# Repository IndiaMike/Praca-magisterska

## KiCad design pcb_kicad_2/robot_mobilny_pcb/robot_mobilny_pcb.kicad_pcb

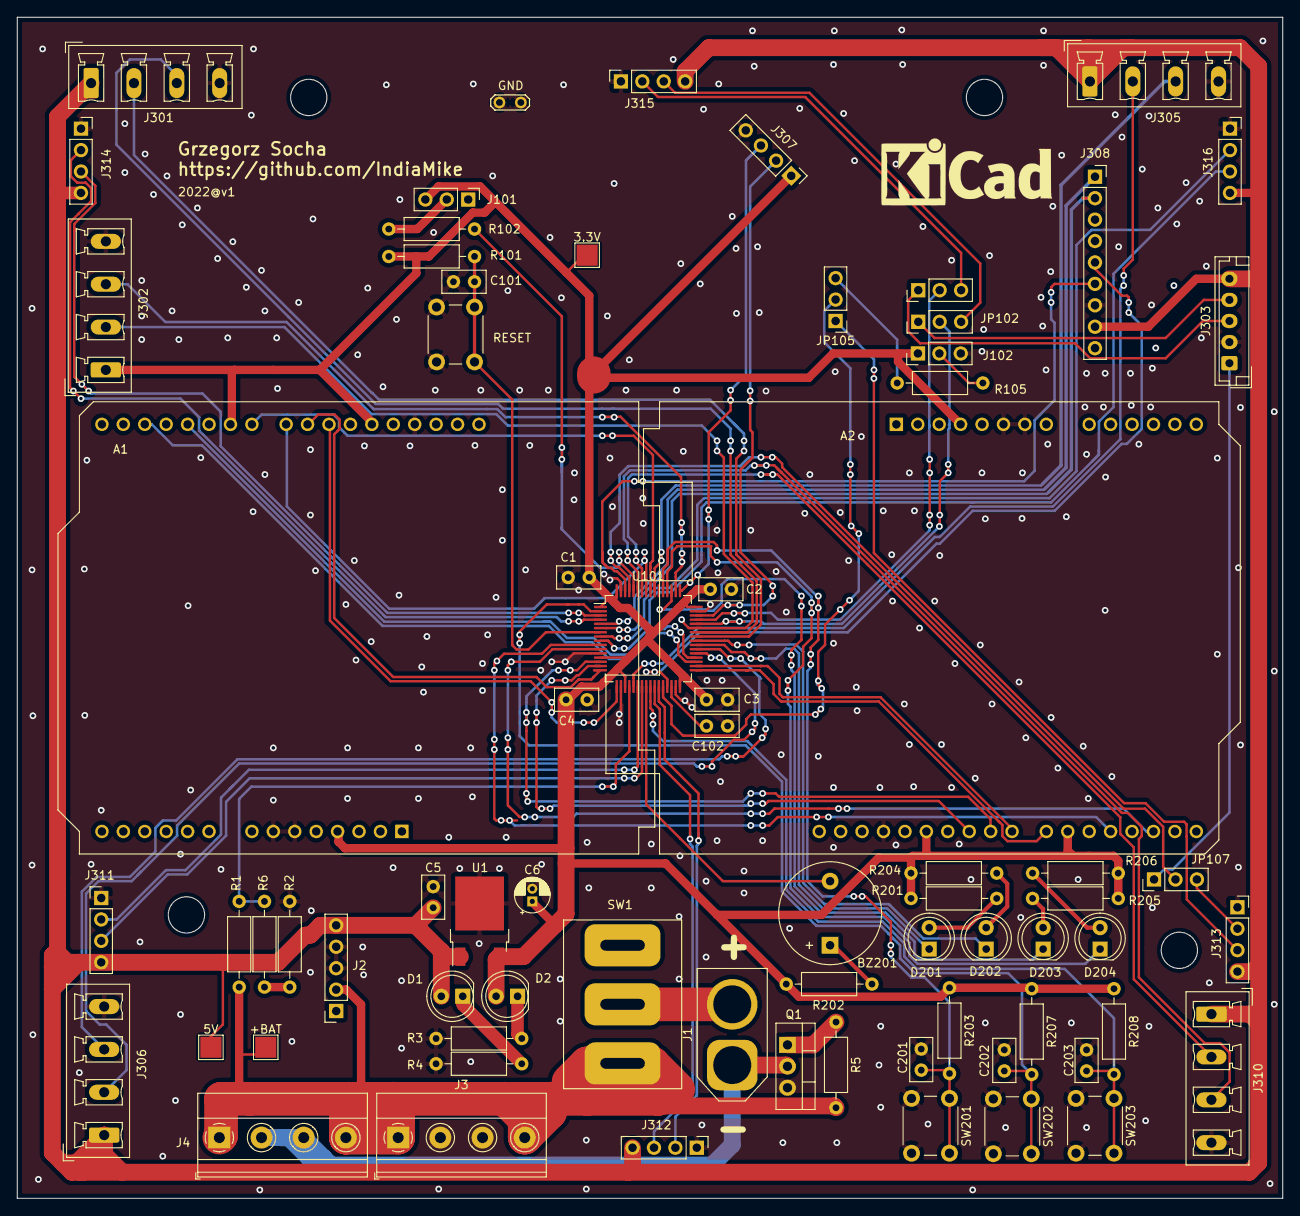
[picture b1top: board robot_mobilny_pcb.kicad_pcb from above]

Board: 2 copper layers, 150.0 x 140.0 mm, 73 parts (0 on the bottom side), 77 nets.

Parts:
3.3V, 5V: T; TestPoint_Pad_2.5x2.5mm
+BAT: T; TestPoint_Pad_2.5x2.5mm
A1, A2: Arduino_UNO_R3
BZ201: Buzzer; Buzzer_12x9.5RM7.6
C1, C2, C3, C4, C5, C101, C201, C202, C203: 100nF; C_Disc_D5.0mm_W2.5mm_P2.50mm
C6: 2,2uF; CP_Radial_D4.0mm_P1.50mm
C102: 4.7uF; C_Disc_D5.0mm_W2.5mm_P2.50mm
D1: RED; LED_D5.0mm
D2: RED2; LED_D5.0mm
D201, D202, D203: LED_G; LED_D5.0mm
D204: LED_Y; LED_D5.0mm
GND: TestPoint_2Pads_Pitch2.54mm_Drill0.8mm
J1: Power 14.8V; AMASS_XT60-M_1x02_P7.20mm_Vertical
J2: STEP_DOWN_D24V50F5; PinSocket_1x05_P2.54mm_Vertical
J3: Motor Driver Power; TerminalBlock_Phoenix_MKDS-1,5-4_1x04_P5.00mm_Horizontal
J4: Motor Driver Power_not_reverse; TerminalBlock_Phoenix_MKDS-1,5-4_1x04_P5.00mm_Horizontal
J101: BOOT0; PinHeader_1x03_P2.54mm_Vertical
J102: BOOT1; PinHeader_1x03_P2.54mm_Vertical
J301: ENCODER_MOT_1; PhoenixContact_MCV_1,5_4-G-5.08_1x04_P5.08mm_Vertical
J302: UART_WIFI; PhoenixContact_MCV_1,5_4-G-5.08_1x04_P5.08mm_Vertical
J303: LIDAR XH2.54-5P; JST_EH_B5B-EH-A_1x05_P2.50mm_Vertical
J305: ENCODER_MOT_2; PhoenixContact_MCV_1,5_4-G-5.08_1x04_P5.08mm_Vertical
J306: ENCODER_MOT_3; PhoenixContact_MCV_1,5_4-G-5.08_1x04_P5.08mm_Vertical
J307: SWD; PinHeader_1x04_P2.54mm_Vertical
J308: LSM303D_acc+mag; PinSocket_1x09_P2.54mm_Vertical
J310: ENCODER_MOT_4; PhoenixContact_MCV_1,5_4-G-5.08_1x04_P5.08mm_Vertical
J311, J312: Conn_01x04_Female; PinHeader_1x04_P2.54mm_Vertical
J313, J314, J315, J316: Conn_01x04_Female; PinSocket_1x04_P2.54mm_Vertical
JP102, JP105, JP107: Jumper_3_Bridged12; PinHeader_1x03_P2.54mm_Vertical
JP104: Zwora; PinHeader_1x03_P2.54mm_Vertical
Q1: IRF540N; TO-220-3_Vertical
R1: 100k; R_Axial_DIN0207_L6.3mm_D2.5mm_P10.16mm_Horizontal
R2, R6, R101, R102, R105: 10k; R_Axial_DIN0207_L6.3mm_D2.5mm_P10.16mm_Horizontal
R3, R4: 470; R_Axial_DIN0207_L6.3mm_D2.5mm_P10.16mm_Horizontal
R5: 47k; R_Axial_DIN0207_L6.3mm_D2.5mm_P10.16mm_Horizontal
R201, R202, R204, R205, R206: 330; R_Axial_DIN0207_L6.3mm_D2.5mm_P10.16mm_Horizontal
R203, R207, R208: 4k7; R_Axial_DIN0207_L6.3mm_D2.5mm_P10.16mm_Horizontal
RESET: RESET; SW_PUSH_6mm_H9.5mm
SW1: SWITCH; Button_MRS-101
SW201: Button_1; SW_PUSH_6mm_H9.5mm
SW202: Button_2; SW_PUSH_6mm_H9.5mm
SW203: Button_3; SW_PUSH_6mm_H9.5mm
U1: LF33_TO252; TO-252-2
U101: STM32F411RETx; LQFP-64_10x10mm_P0.5mm

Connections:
+3V3: 3.3V.1, A1.4, A1.21, A1.27, A2.4, A2.21, A2.27, C1.1, C2.1, C3.1, C4.1, C6.1, D2.2, J101.3, J102.1, J302.1, J307.1, R101.2, R201.2, R202.1, R203.1, R204.2, R205.2, R206.2, R207.1, R208.1, U1.3, U101.1, U101.13, U101.19, U101.32, U101.48, U101.64
+5V: 5V.1, C5.1, D1.2, J2.5, J301.1, J303.5, J305.1, J306.1, J308.8, J310.1, J311.4, J312.4, J313.4, J314.4, J315.4, J316.4, U1.1
+BATT: +BAT.1, J2.2, J3.1, J3.4, J4.1, J4.4, R1.1, R5.2, SW1.3
ADC_BAT: R1.2, R2.1, U101.20
BOOT0: R102.1, U101.60
BUTTON_1: C201.2, R203.2, SW201.1, U101.53
BUTTON_2: C202.2, R207.2, SW202.1, U101.2
BUTTON_3: C203.2, R208.2, SW203.1, U101.25
BUZZER: BZ201.2, U101.24
Dist_Sens_01_Echo: J311.2, U101.22
Dist_Sens_01_Trig: J311.3, U101.23
Dist_Sens_02_Echo: J312.2, U101.27
Dist_Sens_02_Trig: J312.3, U101.26
Dist_Sens_03_Echo: J313.2, JP107.3
Dist_Sens_03_Trig: J313.3, JP105.1
Dist_Sens_04_Echo: J314.2, U101.4
Dist_Sens_04_Trig: J314.3, U101.3
Dist_Sens_05_Echo: J316.2, U101.8
Dist_Sens_05_Trig: J316.3, U101.9
Dist_Sens_06_Echo: J315.2, JP104.3
Dist_Sens_06_Trig: J315.3, JP102.3
ENCODER_1_A: J301.2, U101.41
ENCODER_1_B: J301.3, U101.42
ENCODER_2_A: J305.2, U101.21
ENCODER_2_B: J305.3, U101.55
ENCODER_3_A: J306.2, U101.37
ENCODER_3_B: J306.3, U101.38
ENCODER_4_A: J310.2, U101.58
ENCODER_4_B: J310.3, U101.59
GND: A1.6, A1.7, A1.29, A2.6, A2.7, A2.29, C1.2, C2.2, C3.2, C4.2, C5.2, C6.2, C101.2, C102.2, C201.1, C202.1, C203.1, GND.1, GND.2, J2.3, J2.4, J3.2, J3.3, J101.1, J102.3, J301.4, J302.4, J303.2, J305.4, J306.4, J307.4, J308.7, J310.4, J311.1, J312.1, J313.1, J314.1, J315.1, J316.1, Q1.3, R3.2, R4.2, R6.2, RESET.2, SW201.2, SW202.2, SW203.2, U1.2, U101.12, U101.18, U101.31, U101.47, U101.63
I2C2_SCL_mag+acc: J308.5, U101.29
I2C2_SDA_mag+acc: J308.6, U101.62
INT1_mag+acc: J308.1, U101.5
INT2_mag+acc: J308.2, U101.6
LED1: D201.1, U101.39
LED2: D202.1, U101.40
LED3: D203.1, U101.51
LED4: D204.1, U101.52
M1INA: A2.17, U101.11
M1INB: A2.19, U101.10
M1PWM: A2.24, U101.14
M2INA: A2.22, U101.33
M2INB: A2.23, U101.34
M2PWM: A2.25, U101.15
M3INA: A1.17, U101.35
M3INB: A1.19, U101.36
M3PWM: A1.24, U101.16
M4INA: A1.22, U101.56
M4INB: A1.23, U101.57
M4PWM: A1.25, U101.17
NRST: C101.1, R101.1, RESET.1, U101.7
unnamed: BZ201.1, R202.2
unnamed: D1.1, R4.1
unnamed: D2.1, R3.1
unnamed: D201.2, R201.1
unnamed: D202.2, R204.1
unnamed: D203.2, R205.1
unnamed: D204.2, R206.1
unnamed: J1.1, J4.2, J4.3, Q1.2
unnamed: J1.2, SW1.2
unnamed: J101.2, R102.2
unnamed: J102.2, R105.2
unnamed: JP105.3, R105.1
unnamed: Q1.1, R5.1
unnamed: R2.2, R6.1
PA11: JP102.2, U101.44
PA12: JP104.2, U101.45
PB2: JP105.2, U101.28
PB9: JP107.2, U101.61
PWM_LIDAR: J303.1, JP107.1
SWCLK: J307.3, U101.49
SWDIO: J307.2, U101.46
UART1_RX: J302.2, U101.43
UART1_TX: J302.3, U101.50
UART6_RX: J303.3, JP104.1
UART6_TX: J303.4, JP102.1
VCAP_1: C102.1, U101.30

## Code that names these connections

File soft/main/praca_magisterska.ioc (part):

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PB13.GPIOParameters=GPIO_Label
PC7.GPIOParameters=GPIO_Label
PC12.Signal=GPIO_Input
PB14.GPIO_Label=M3INA
PC6.GPIO_Label=ENCODER_3_A
PA3.GPIOParameters=GPIO_Label
PB6.GPIO_Label=ENCODER_4_B
PA12.GPIO_ModeDefaultEXTI=GPIO_MODE_IT_RISING_FALLING
PB13.Signal=GPIO_Output
PA2.GPIOParameters=GPIO_Label
PC15-OSC32_OUT.GPIO_Label=SENS_LEFT_E
RCC.SYSCLKSource=RCC_SYSCLKSOURCE_PLLCLK
PB6.Signal=S_TIM4_CH1
PC7.Signal=S_TIM3_CH2
PC3.Signal=GPIO_Output
PC13-ANTI_TAMP.Signal=GPIO_Input
PB12.GPIO_Label=M2INA
PA1.GPIOParameters=GPIO_Label
PC4.GPIO_Label=BUZZER
PA8.Signal=S_TIM1_CH1
PC0.GPIO_ModeDefaultEXTI=GPIO_MODE_IT_RISING_FALLING
PC8.GPIOParameters=GPIO_Label
Mcu.Package=LQFP64
PA10.Signal=USART1_RX
PA5.GPIOParameters=GPIO_Label
PB14.GPIOParameters=GPIO_Label
PC15-OSC32_OUT.GPIOParameters=GPIO_Label,GPIO_ModeDefaultEXTI
PA4.GPIO_Label=ADC_BAT
PC4.GPIOParameters=GPIO_Label
PA15.GPIOParameters=GPIO_Label
PC13-ANTI_TAMP.GPIO_Label=BUTTON_2
PA9.GPIO_Label=ENCODER_1_B
PC2.Signal=GPIO_Output
PC6.Signal=S_TIM3_CH1
PA11.GPIO_Label=SENS_FRONT_T
PC0.Signal=GPXTI0
PC14-OSC32_IN.Signal=GPIO_Output
PC11.GPIOParameters=GPIO_Label
PA0-WKUP.GPIO_Label=M1PWM
PA0-WKUP.Signal=S_TIM5_CH1
PC3.GPIOParameters=GPIO_Label
PB8.GPIO_Label=PWM_LIDAR
PA8.GPIO_Label=ENCODER_1_A
PA9.Signal=S_TIM1_CH2
PB14.Signal=GPIO_Output
PA5.Signal=S_TIM2_CH1_ETR
PB4.GPIO_Label=M4INA
PB15.GPIO_Label=M3INB
PC2.GPIOParameters=GPIO_Label
PA1.GPIO_Label=M2PWM
PC10.GPIOParameters=GPIO_Label
PC9.GPIOParameters=GPIO_Label
PC7.GPIO_Label=ENCODER_3_B
PA4.Signal=ADCx_IN4
PB5.Signal=GPIO_Output
PA5.GPIO_Label=ENCODER_2_A
PC12.GPIO_Label=BUTTON_1
PA11.Signal=GPIO_Output
PC3.GPIO_Label=M1INA
PC1.Signal=GPIO_Output
PB12.GPIOParameters=GPIO_Label
Mcu.UserName=STM32F411RETx
PC10.Signal=GPIO_Output
PA12.GPIOParameters=GPIO_Label,GPIO_ModeDefaultEXTI
PC0.GPIOParameters=GPIO_Label,GPIO_ModeDefaultEXTI
PA9.GPIOParameters=GPIO_Label
PA11.GPIOParameters=GPIO_Label
PC0.GPIO_Label=SENS_RIGHT_E
PB13.GPIO_Label=M2INB
PB15.Signal=GPIO_Output
PB5.GPIOParameters=GPIO_Label
PA15.GPIO_Label=UART1_WIFI_TX
PB4.GPIOParameters=GPIO_Label
PA12.Signal=GPXTI12
PC1.GPIOParameters=GPIO_Label
PA8.GPIOParameters=GPIO_Label
PA0-WKUP.GPIOParameters=GPIO_Label
RCC.HSE_VALUE=25000000
PA15.Mode=Asynchronous
PC15-OSC32_OUT.GPIO_ModeDefaultEXTI=GPIO_MODE_IT_RISING_FALLING
PC11.GPIO_Label=LED_4
PA10.GPIO_Label=UART1_WIFI_RX
PB3.GPIOParameters=GPIO_Label
PB7.Signal=S_TIM4_CH2
PB6.GPIOParameters=GPIO_Label
PC14-OSC32_IN.GPIOParameters=GPIO_Label
PB7.GPIO_Label=ENCODER_4_A
PA2.GPIO_Label=M3PWM
PA15.Signal=USART1_TX
PB5.GPIO_Label=M4INB
PC14-OSC32_IN.GPIO_Label=SENS_LEFT_T
PC5.Signal=GPIO_Input
PC2.GPIO_Label=M1INB
PB4.Signal=GPIO_Output
PA3.Signal=S_TIM5_CH4
PC13-ANTI_TAMP.GPIOParameters=GPIO_Label
PB3.GPIO_Label=ENCODER_2_B
PB8.GPIOParameters=GPIO_Label
PC10.GPIO_Label=LED_3
PA10.Mode=Asynchronous
PC9.GPIO_Label=LED_2
PC11.Signal=GPIO_Output
PC8.Signal=GPIO_Output
PC4.Signal=GPIO_Output
PA12.GPIO_Label=SENS_FRONT_E
PC8.GPIO_Label=LED_1
PC12.GPIOParameters=GPIO_Label
PB7.GPIOParameters=GPIO_Label
PC5.GPIOParameters=GPIO_Label
PC15-OSC32_OUT.Signal=GPXTI15
PA1.Signal=S_TIM5_CH2
board=custom
PA10.GPIOParameters=GPIO_Label
PC1.GPIO_Label=SENS_RIGHT_T
PA4.GPIOParameters=GPIO_Label
PB15.GPIOParameters=GPIO_Label
Mcu.Name=STM32F411R(C-E)Tx
PA2.Signal=S_TIM5_CH3
PB3.Signal=S_TIM2_CH2
RCC.SYSCLKFreq_VALUE=100000000
PC5.GPIO_Label=BUTTON_3
PC6.GPIOParameters=GPIO_Label
PB8.Signal=S_TIM10_CH1
PC9.Signal=GPIO_Output
PB12.Signal=GPIO_Output
PA3.GPIO_Label=M4PWM

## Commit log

2021-12-10 schematic update
2021-12-15 schematic_update
2021-12-19 PCB_update
    Change of motor controller connector to Arduino shields
2022-01-13 PCB_update
2022-03-16 clear
2022-03-18 pcb2
2022-03-23 pcb v2
    version 2 (shorter)
2022-03-30 pre_order
2022-04-26 cleaning
2022-04-26 Motors & Encoders
2022-05-06 wifi_Uart
2022-05-17 encoder speed calculation
2022-05-22 PID_1
2022-05-22 buttons & leds update
2022-05-24 PID p implementation
2022-05-26 backup
2022-05-26 pid_cd
2022-05-31 cleaning delete pid
2022-05-31 pid update
2022-05-31 solidworks
2022-06-01 all motors
    Motor 1 problem
2022-06-01 Robot_structure
2022-06-02 position_PID_vol1
2022-06-02 forward_pid vol2
2022-06-02 vol3.0
2022-06-07 pid & position update
    konsultacje
2022-06-10 motor break
2022-06-24 big commit
2022-06-27 Qt transmision Wifi
2022-06-28 receive UART circular buffer
2022-06-28 konsultacje distance & direction regulator
2022-08-15 simple parser
2022-08-15 parser complex example test
2022-08-15 comands to parser
2022-08-15 QT communication
2022-08-16 LIDAR
2022-08-17 A_star_qt
2022-08-19 Lipol protection
2022-08-20 few :D Robot mode fix, watchdog, Error communications
2022-08-20 PID switching off when not use
2022-08-20 safe zone in Qt
2022-08-21 qt map
2022-08-23 big commit qt path, Robot path go
2022-08-23 floodfillQt
2022-08-24 kp-motor
2022-08-27 distance_sensorFront
2022-08-30 qt floodfill
2022-09-01 sensors
2022-09-01 obstaccle_sensors
2022-09-02 finish codding
2022-09-03 apperance Qt, Word
